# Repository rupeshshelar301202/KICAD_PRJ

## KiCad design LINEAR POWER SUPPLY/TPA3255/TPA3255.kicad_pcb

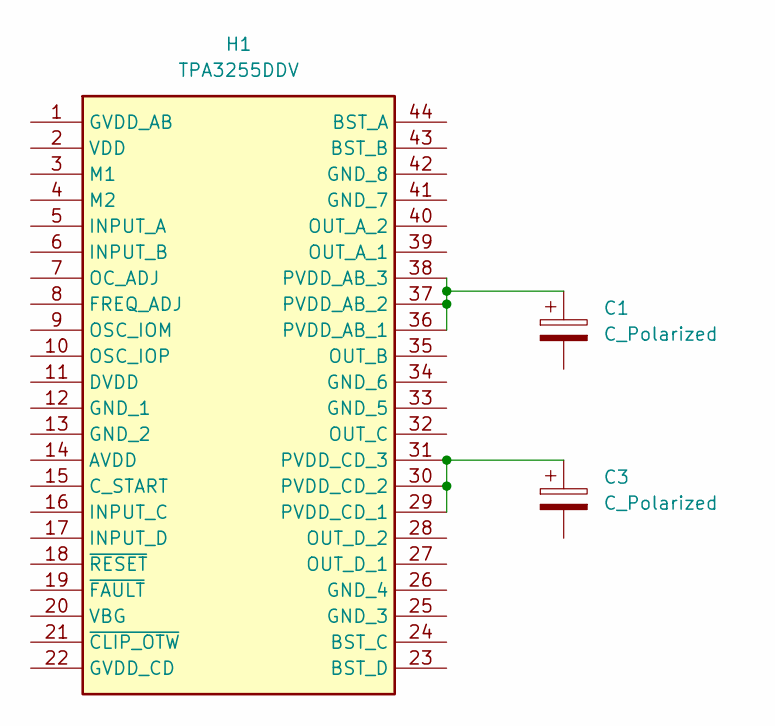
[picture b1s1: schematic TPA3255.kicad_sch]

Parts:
C1, C3: C_Polarized; CP_Radial_D35.0mm_P10.00mm_SnapIn
H1: TPA3255DDV; SOP64P810X120-44N; Manufacturer_Part_Number TPA3255DDV; Mouser Part Number 595-TPA3255DDV

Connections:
unnamed: C1.1, H1.36 (PVDD_AB_1), H1.37 (PVDD_AB_2), H1.38 (PVDD_AB_3)
unnamed: C3.1, H1.29 (PVDD_CD_1), H1.30 (PVDD_CD_2), H1.31 (PVDD_CD_3)

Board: 2 copper layers, 3 parts (0 on the bottom side), 2 nets, no tracks yet.

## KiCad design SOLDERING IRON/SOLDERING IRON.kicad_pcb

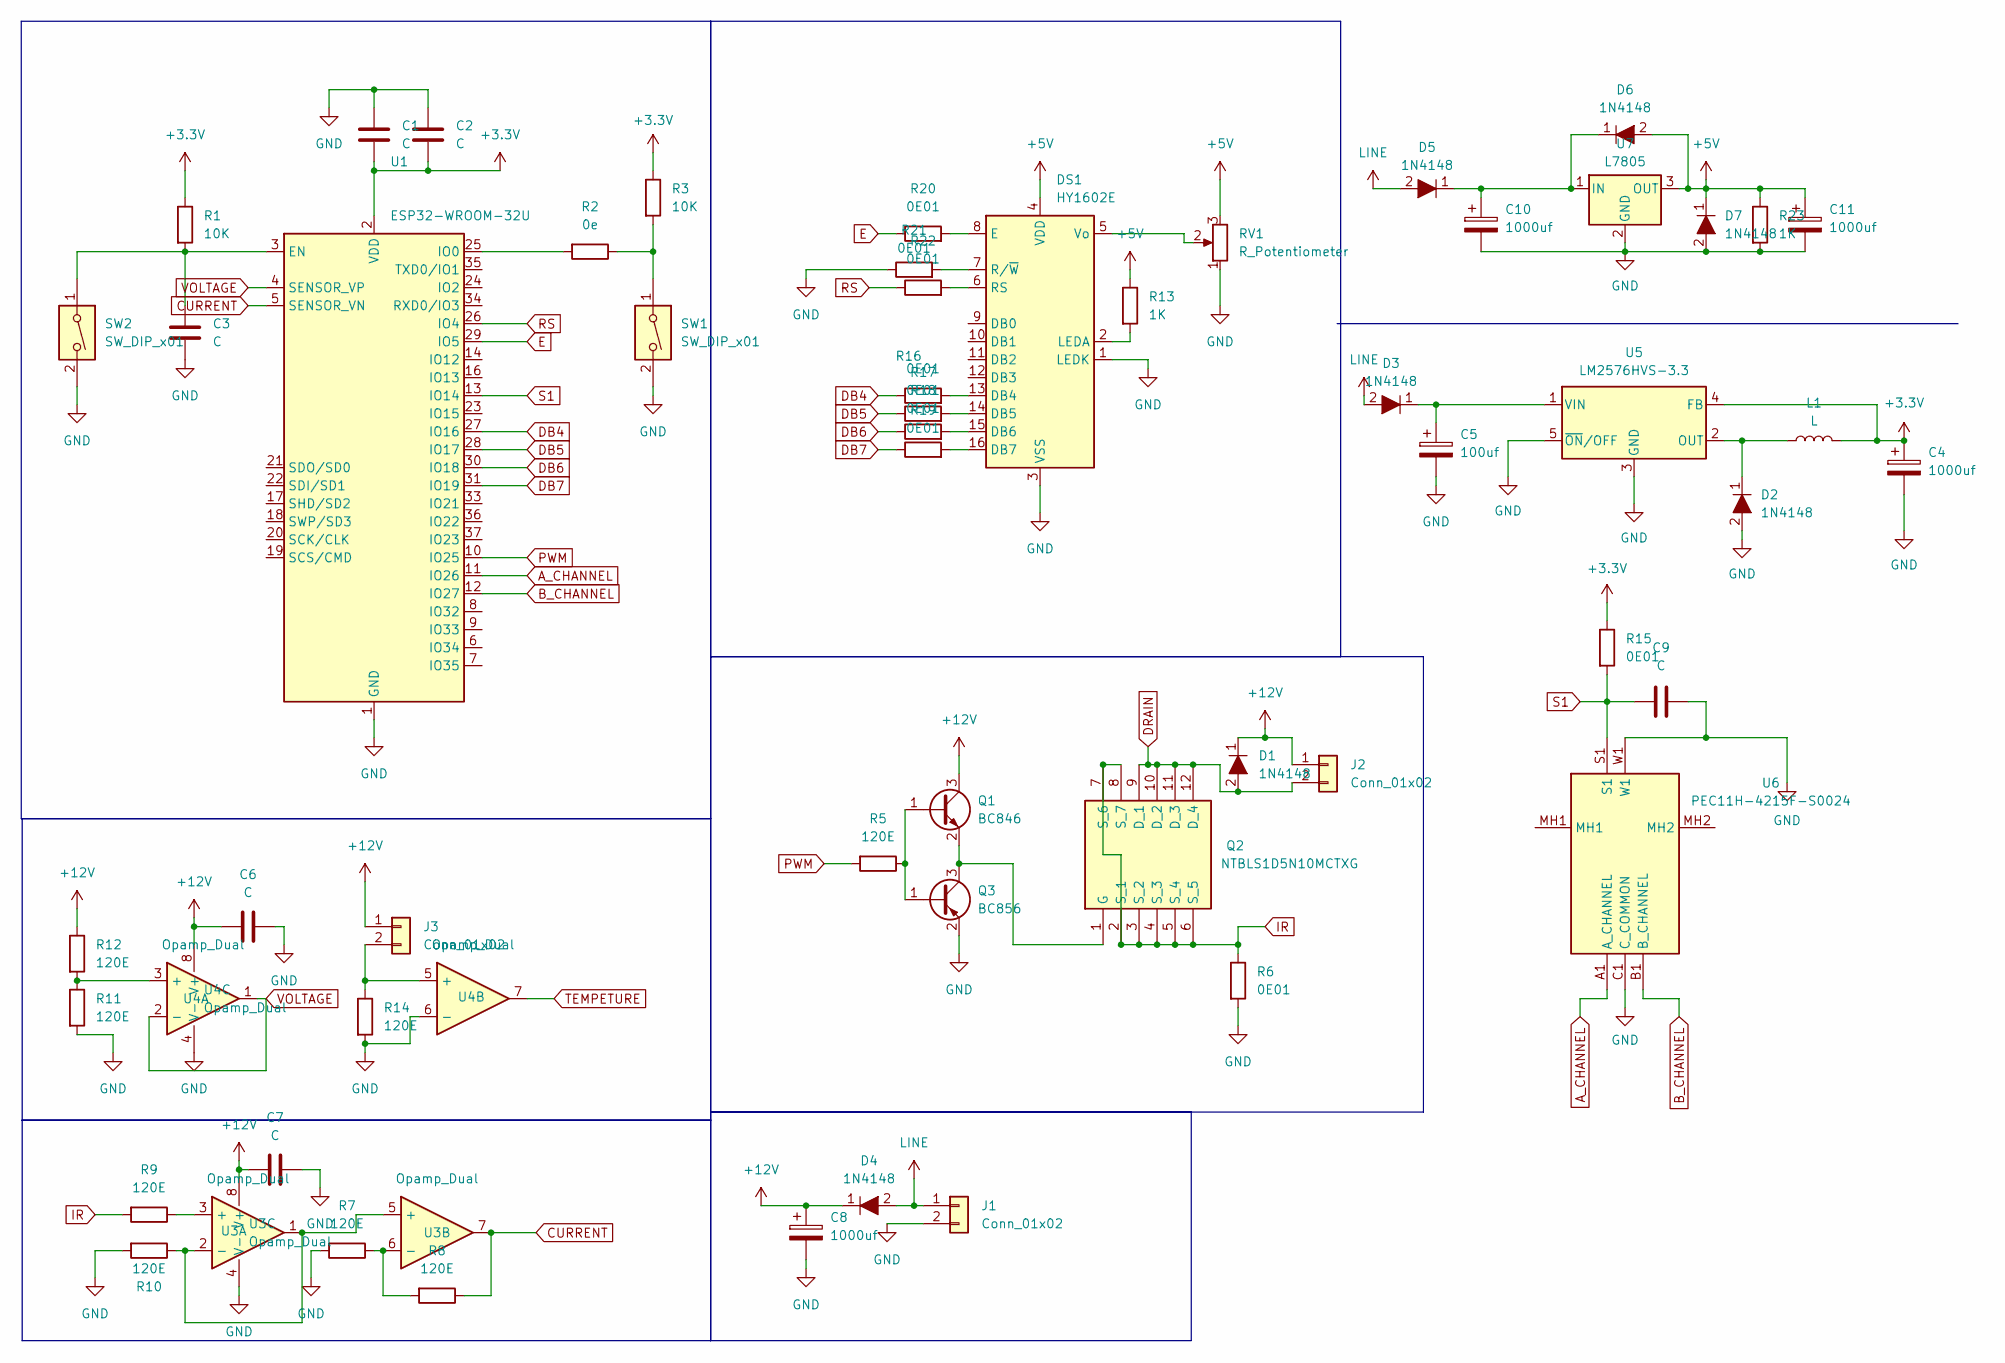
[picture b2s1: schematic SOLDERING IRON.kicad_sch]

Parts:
C1, C2, C3, C6, C7, C9: C; C_1206_3216Metric_Pad1.33x1.80mm_HandSolder
C4, C8, C10, C11: 1000uf; C_1206_3216Metric_Pad1.33x1.80mm_HandSolder
C5: 100uf; C_1206_3216Metric_Pad1.33x1.80mm_HandSolder
D1, D2, D3, D4, D5, D6, D7: 1N4148; D_SMC_Handsoldering; MPN 1N4148; Digi-Key_PN 1N4148FS-ND
DS1: HY1602E
J1, J2, J3: Conn_01x02; TerminalBlock_Phoenix_MKDS-1,5-2-5.08_1x02_P5.08mm_Horizont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
L1: L; L_Coilcraft_MSS1278-XXX
Q1: BC846; SOT-23_Handsoldering
Q2: NTBLS1D5N10MCTXG; NVBLS0D8N08XTXG; Mouser Part Number 863-NTBLS1D5N10MCTXG
Q3: BC856; SOT-23_Handsoldering
R1, R3: 10K; R_1206_3216Metric_Pad1.30x1.75mm_HandSolder
R2: 0e; R_1206_3216Metric_Pad1.30x1.75mm_HandSolder
R5, R7, R8, R9, R10, R11, R12, R14: 120E; R_1206_3216Metric_Pad1.30x1.75mm_HandSolder
R6, R15, R16, R17, R18, R19, R20, R21, R22: 0E01; R_1206_3216Metric_Pad1.30x1.75mm_HandSolder
R13, R23: 1K; R_1206_3216Metric_Pad1.30x1.75mm_HandSolder
RV1: R_Potentiometer; Potentiometer_Bourns_3386C_Horizontal
SW1, SW2: SW_DIP_x01; SW_PUSH_6mm_H7.3mm
U1: ESP32-WROOM-32U
U3, U4: Opamp_Dual; DIP-8_W7.62mm
U5: LM2576HVS-3.3; TO-263-5_TabPin3
U6: PEC11H-4215F-S0024; PEC11H4215FS0024; Mouser Part Number 652-PEC11H4215FS0024
U7: L7805; TO-220-3_Horizontal_TabDown

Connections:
+3.3V: C1.2, C2.2, C4.1, L1.2, R1.1, R3.1, R15.1, U1.2 (VDD), U5.4 (FB)
+5V: C11.1, D6.2, D7.1, DS1.4 (VDD), R13.1, R23.1, RV1.3, U7.3 (OUT)
+12V: C6.1, C7.1, C8.1, D1.1, D4.1, J2.1, J3.1, Q1.3 (C), R12.1, U3.8 (V+), U4.8 (V+)
A_CHANNEL: U1.11 (IO26), U6.A1 (A_CHANNEL)
B_CHANNEL: U1.12 (IO27), U6.B1 (B_CHANNEL)
CURRENT: R8.1, U1.5 (SENSOR_VN), U3.7
DB4: R16.1, U1.27 (IO16)
DB5: R17.1, U1.28 (IO17)
DB6: R18.1, U1.30 (IO18)
DB7: R19.1, U1.31 (IO19)
DRAIN: D1.2, J2.2, Q2.9 (D_1), Q2.10 (D_2), Q2.11 (D_3), Q2.12 (D_4)
E: R20.1, U1.29 (IO5)
GND: C1.1, C2.1, C3.2, C4.2, C5.2, C6.2, C7.2, C8.2, C9.2, C10.2, C11.2, D2.2, D7.2, DS1.1 (LEDK), DS1.3 (VSS), J1.2, Q3.2 (E), R6.2, R7.2, R10.2, R11.2, R14.2, R21.1, R23.2, RV1.1, SW1.2, SW2.2, U1.1 (GND), U1.15 (GND), U1.38 (GND), U1.39 (GND), U3.4 (V-), U4.4 (V-), U4.6 (-), U5.3 (GND), U5.5 (~ON/OFF), U6.C1 (C_COMMON), U6.W1, U7.2 (GND)
IR: Q2.2 (S_1), Q2.3 (S_2), Q2.4 (S_3), Q2.5 (S_4), Q2.6 (S_5), Q2.7 (S_6), Q2.8 (S_7), R6.1, R9.2
LINE: D3.2, D4.2, D5.2, J1.1
unnamed: DS1.13 (DB4), R16.2
unnamed: DS1.14 (DB5), R17.2
unnamed: DS1.15 (DB6), R18.2
unnamed: DS1.16 (DB7), R19.2
unnamed: DS1.8 (E), R20.2
unnamed: DS1.2 (LEDA), R13.2
unnamed: DS1.6 (RS), R22.2
unnamed: DS1.7 (R/~W), R21.2
unnamed: DS1.5 (Vo), RV1.2
unnamed: J3.2, R14.1, U4.5 (+)
unnamed: Q1.1 (B), Q3.1 (B), R5.1
unnamed: Q1.2 (E), Q2.1 (G), Q3.3 (C)
unnamed: R2.1, R3.2, SW1.1
unnamed: C3.1, R1.2, SW2.1, U1.3 (EN)
unnamed: R2.2, U1.25 (IO0)
unnamed: R9.1, U3.3 (+)
unnamed: R10.1, U3.1, U3.2 (-), U3.5 (+)
unnamed: R7.1, R8.2, U3.6 (-)
unnamed: R11.1, R12.2, U4.3 (+)
unnamed: D2.1, L1.1, U5.2 (OUT)
unnamed: C5.1, D3.1, U5.1 (VIN)
unnamed: C10.1, D5.1, D6.1, U7.1 (IN)
PWM: R5.2, U1.10 (IO25)
RS: R22.1, U1.26 (IO4)
S1: C9.1, R15.2, U1.13 (IO14), U6.S1
TEMPETURE: U4.7
VOLTAGE: U1.4 (SENSOR_VP), U4.1, U4.2 (-)

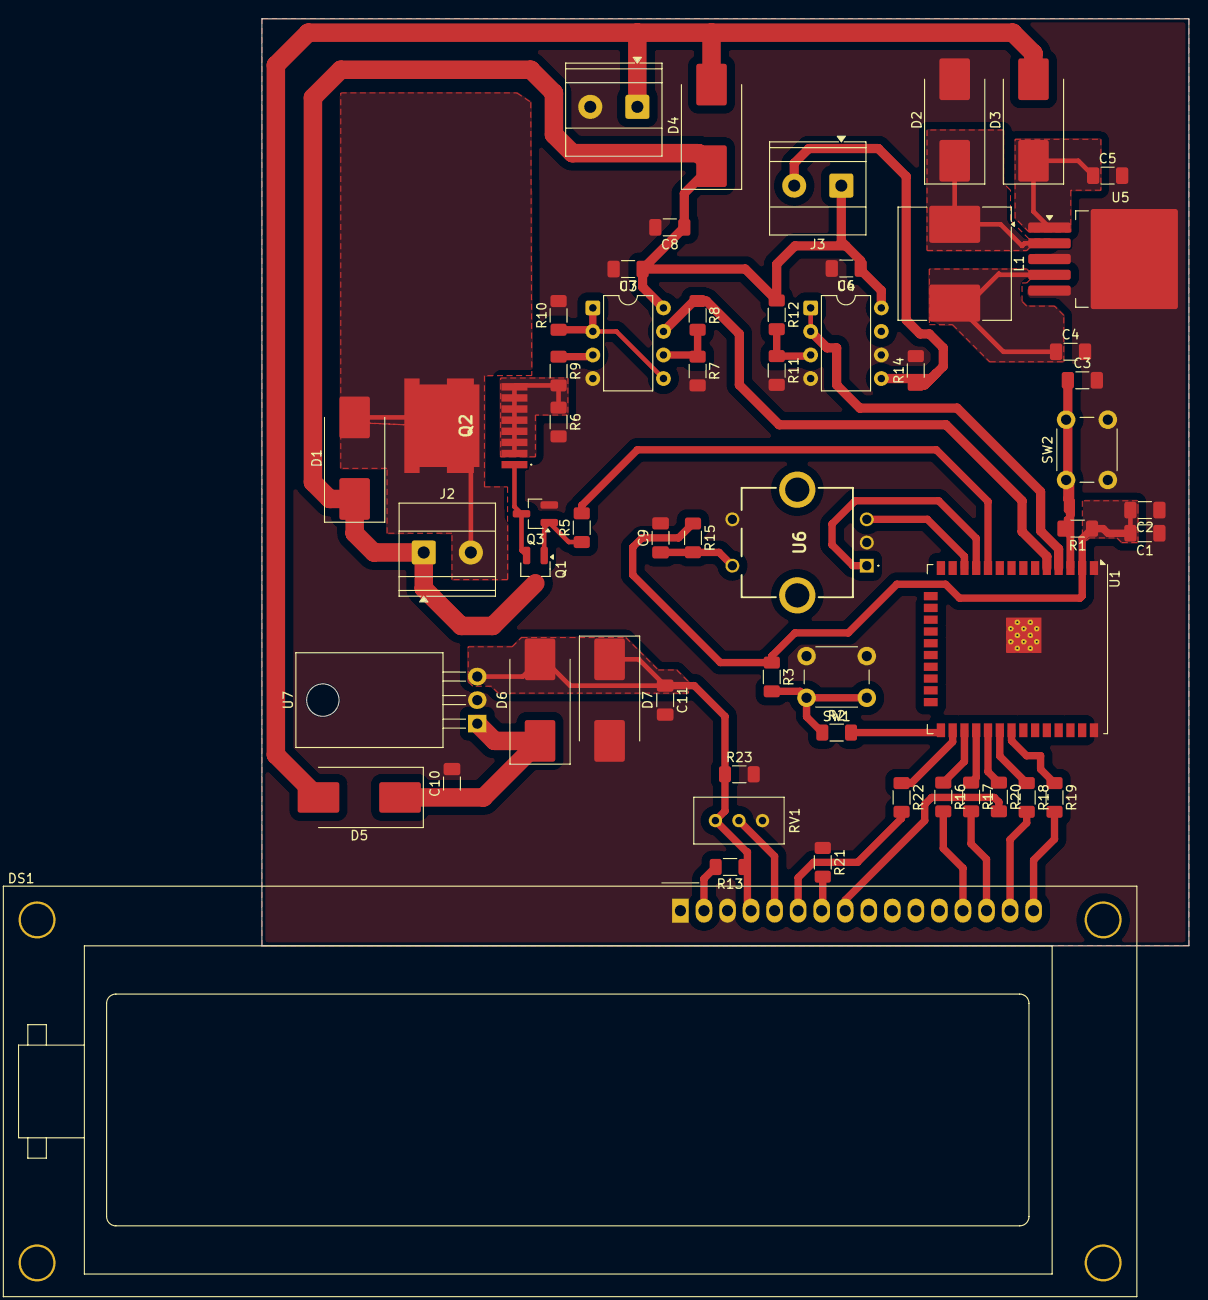
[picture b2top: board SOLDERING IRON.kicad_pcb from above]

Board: 2 copper layers, 100.0 x 100.0 mm, 57 parts (0 on the bottom side), 41 nets.

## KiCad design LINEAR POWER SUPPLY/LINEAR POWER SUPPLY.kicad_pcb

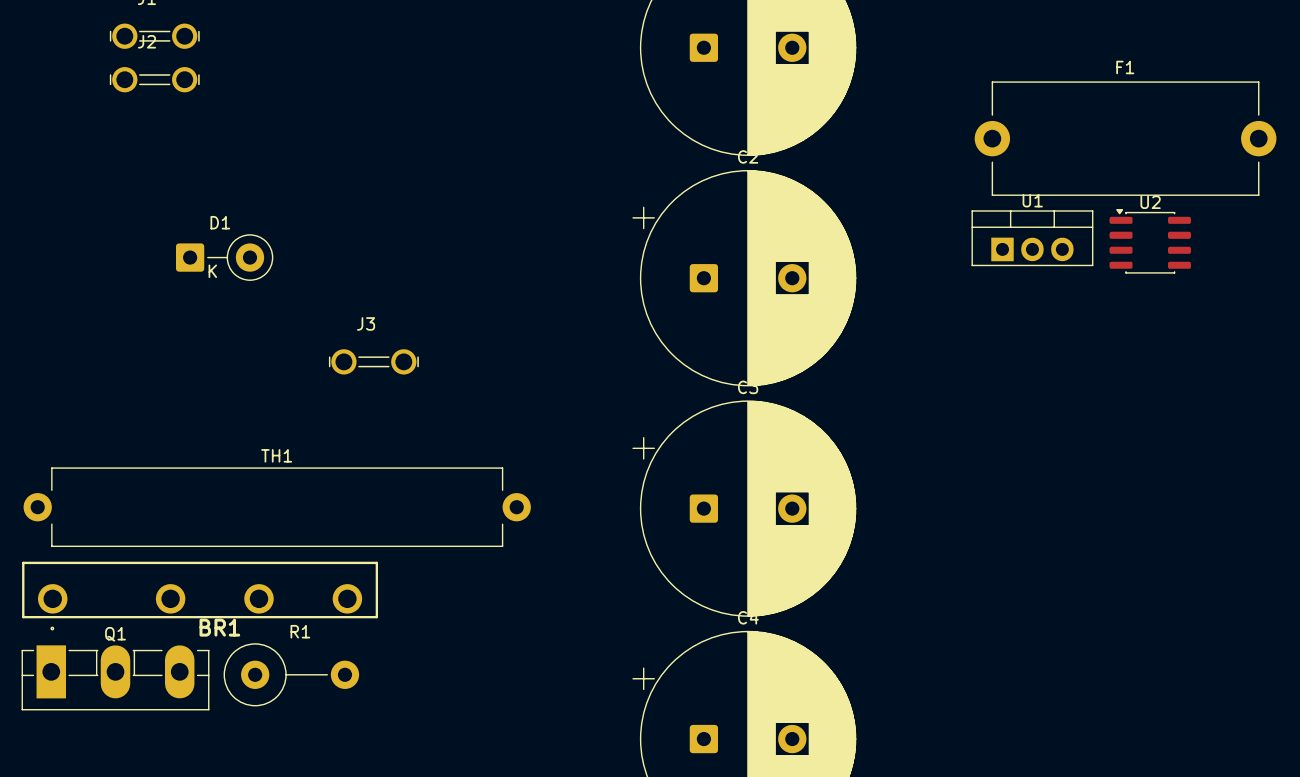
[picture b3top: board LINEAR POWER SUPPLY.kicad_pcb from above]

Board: 2 copper layers, 15 parts (0 on the bottom side), 11 nets, no tracks yet.

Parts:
BR1: GBJ2510-F; GBJ_1
C1, C2, C3, C4: 2200UF/100V; CP_Radial_D18.0mm_P7.50mm
D1: D_Zener_Filled; D_DO-15_P5.08mm_Vertical_KathodeUp
F1: Fuse_Small; Fuseholder_Cylinder-5x20mm_Stelvio-Kontek_PTF78_Horizontal_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
J1, J2, J3: SPADE; TE_62409-1
Q1: 2SB817; TO-3PB-3_Vertical
R1: R; R_Axial_DIN0516_L15.5mm_D5.0mm_P7.62mm_Vertical
TH1: Thermistor_NTC; R_Axial_Power_L38.0mm_W6.4mm_P40.64mm
U1: LM317_TO-220; TO-220-3_Vertical
U2: ACS712xLCTR-05B; SOIC-8_3.9x4.9mm_P1.27mm

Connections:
+DC: C1.1, C2.1, Q1.2 (C), R1.1, TH1.2
-DC: BR1.4 (-), C3.2, C4.2
GND: C1.2, C2.2, C3.1, C4.1, J3.1, U2.5 (GND)
unnamed: BR1.1 (+), F1.1
unnamed: D1.2 (A), U1.2 (VO), U2.1 (IP+), U2.2 (IP+)
unnamed: D1.1 (K), Q1.1 (B), R1.2
unnamed: Q1.3 (E), U1.3 (VI)
unnamed: F1.2, TH1.1
unnamed: BR1.3, J1.1
unnamed: BR1.2, J2.1
unnamed: U2.3 (IP-), U2.4 (IP-)

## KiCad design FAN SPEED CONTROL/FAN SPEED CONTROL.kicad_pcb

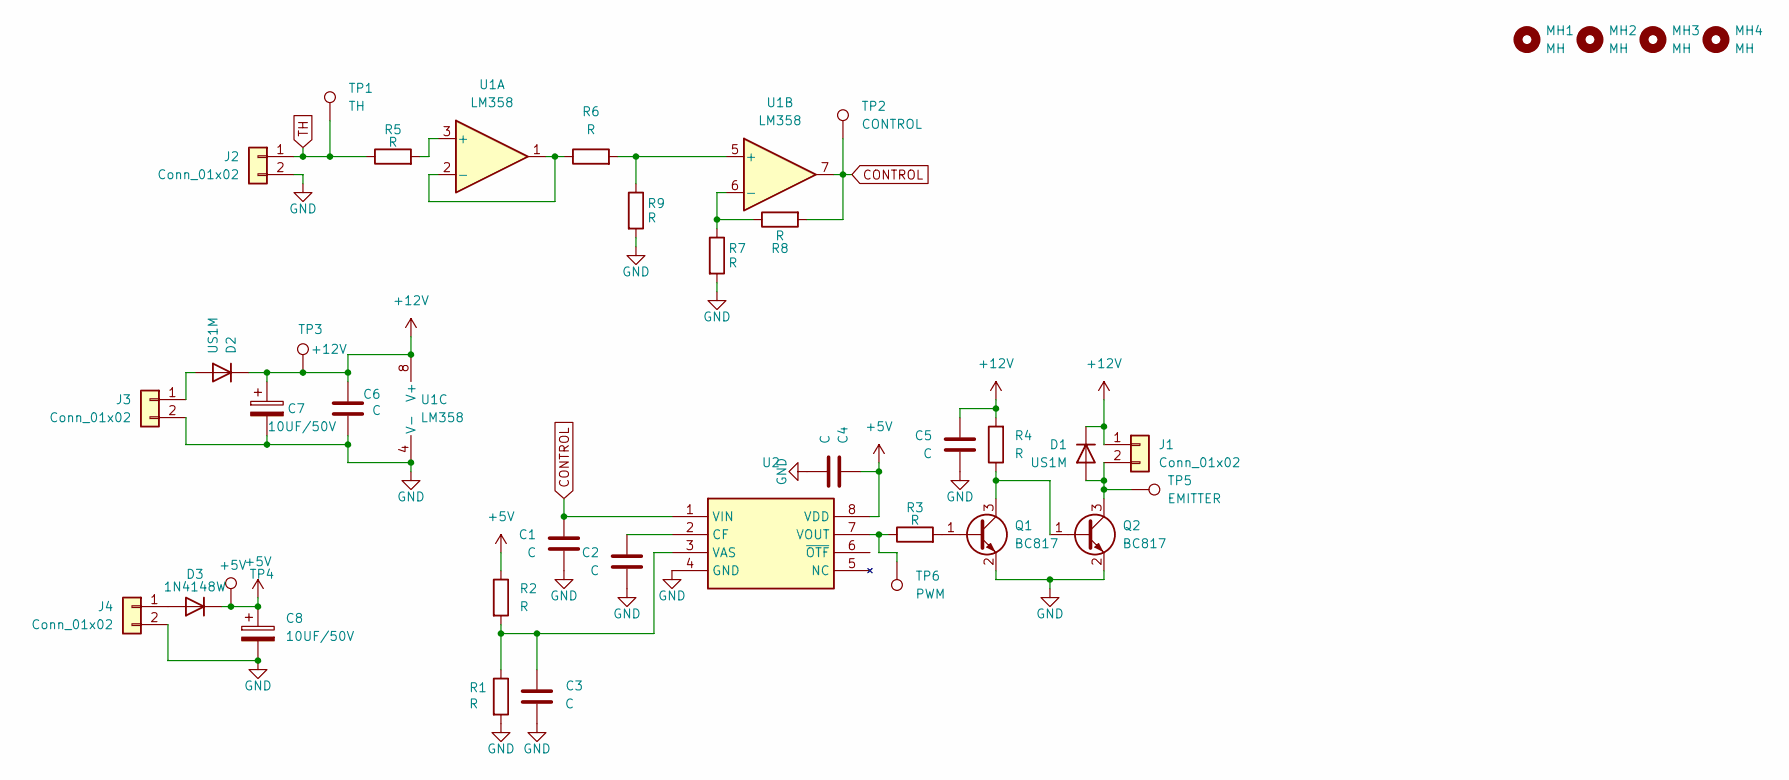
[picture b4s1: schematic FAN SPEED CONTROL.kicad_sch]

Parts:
C1, C2, C3, C4, C5: C; C_0603_1608Metric_Pad1.08x0.95mm_HandSolder
C6: C; C_1206_3216Metric_Pad1.33x1.80mm_HandSolder
C7, C8: 10UF/50V; CP_Radial_D5.0mm_P2.00mm
D1, D2: US1M; D_SMA
D3: 1N4148W; D_SOD-123
J1, J2, J3, J4: Conn_01x02; Molex_KK-254_AE-6410-02A_1x02_P2.54mm_Vertical
MH1, MH2, MH3, MH4: MH; MountingHole_3.5mm_Pad_Via
Q1, Q2: BC817; SOT-23
R1, R2, R3, R4, R5, R6, R7, R8, R9: R; R_0603_1608Metric_Pad0.98x0.95mm_HandSolder
TP1: TH; TestPoint_Pad_D3.0mm
TP2: CONTROL; TestPoint_Pad_D3.0mm
TP3: +12V; TestPoint_Pad_D3.0mm
TP4: +5V; TestPoint_Pad_D3.0mm
TP5: EMITTER; TestPoint_Pad_D3.0mm
TP6: PWM; TestPoint_Pad_D3.0mm
U1: LM358; SOIC-8_3.9x4.9mm_P1.27mm
U2: TC648BEOA; SOIC127P600X175-8N; Manufacturer_Part_Number TC648BEOA; Mouser Part Number 579-TC648BEOA

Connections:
+5V: C4.1, C8.1, D3.1 (K), R2.1, TP4.1, U2.8 (VDD)
+12V: C5.1, C6.1, C7.1, D1.1 (K), D2.1 (K), J1.1, R4.2, TP3.1, U1.8 (V+)
CONTROL: C1.1, R8.2, TP2.1, U1.7, U2.1 (VIN)
GND: C1.2, C2.2, C3.2, C4.2, C5.2, C6.2, C7.2, C8.2, J2.2, J3.2, J4.2, Q1.2 (E), Q2.2 (E), R1.2, R7.2, R9.2, U1.4 (V-), U2.4 (GND)
unnamed: D1.2 (A), J1.2, Q2.3 (C), TP5.1
unnamed: D2.2 (A), J3.1
unnamed: D3.2 (A), J4.1
unnamed: Q1.1 (B), R3.2
unnamed: Q1.3 (C), Q2.1 (B), R4.1
unnamed: R5.2, U1.3 (+)
unnamed: R6.1, U1.1, U1.2 (-)
unnamed: R6.2, R9.1, U1.5 (+)
unnamed: R7.1, R8.1, U1.6 (-)
unnamed: C2.1, U2.2 (CF)
unnamed: C3.1, R1.1, R2.2, U2.3 (VAS)
unnamed: R3.1, TP6.1, U2.7 (VOUT)
TH: J2.1, R5.1, TP1.1

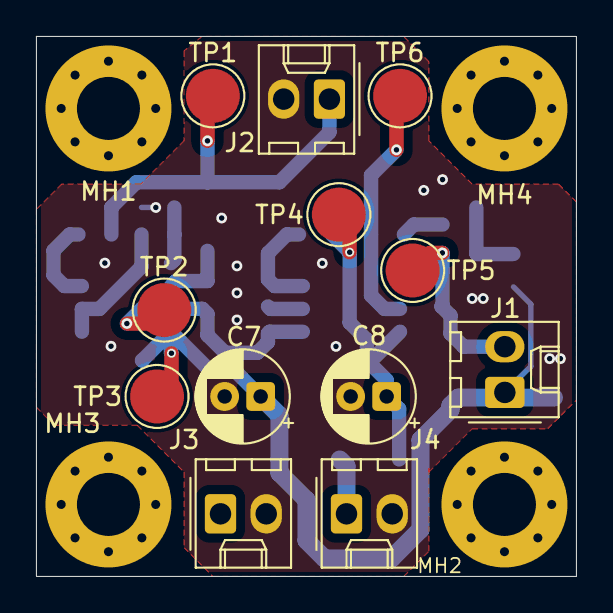
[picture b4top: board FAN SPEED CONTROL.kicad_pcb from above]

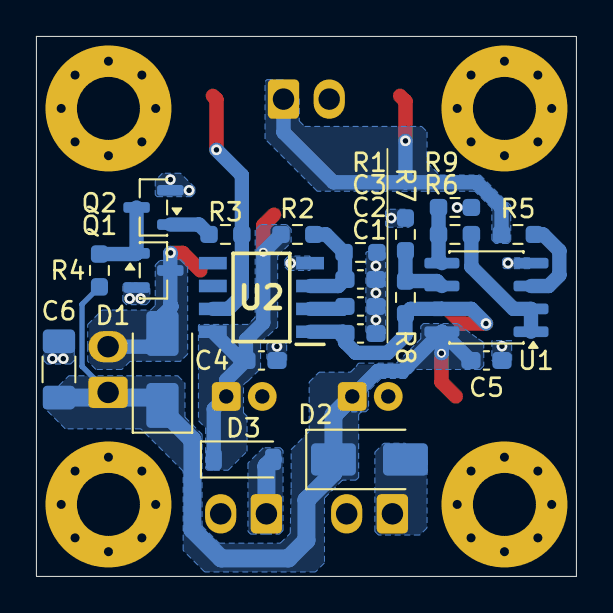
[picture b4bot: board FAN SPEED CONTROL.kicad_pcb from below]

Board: 2 copper layers, 30.0 x 30.0 mm, 38 parts (22 on the bottom side), 17 nets.

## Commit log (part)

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2025-11-30 delete
2026-01-04 sdfasf
